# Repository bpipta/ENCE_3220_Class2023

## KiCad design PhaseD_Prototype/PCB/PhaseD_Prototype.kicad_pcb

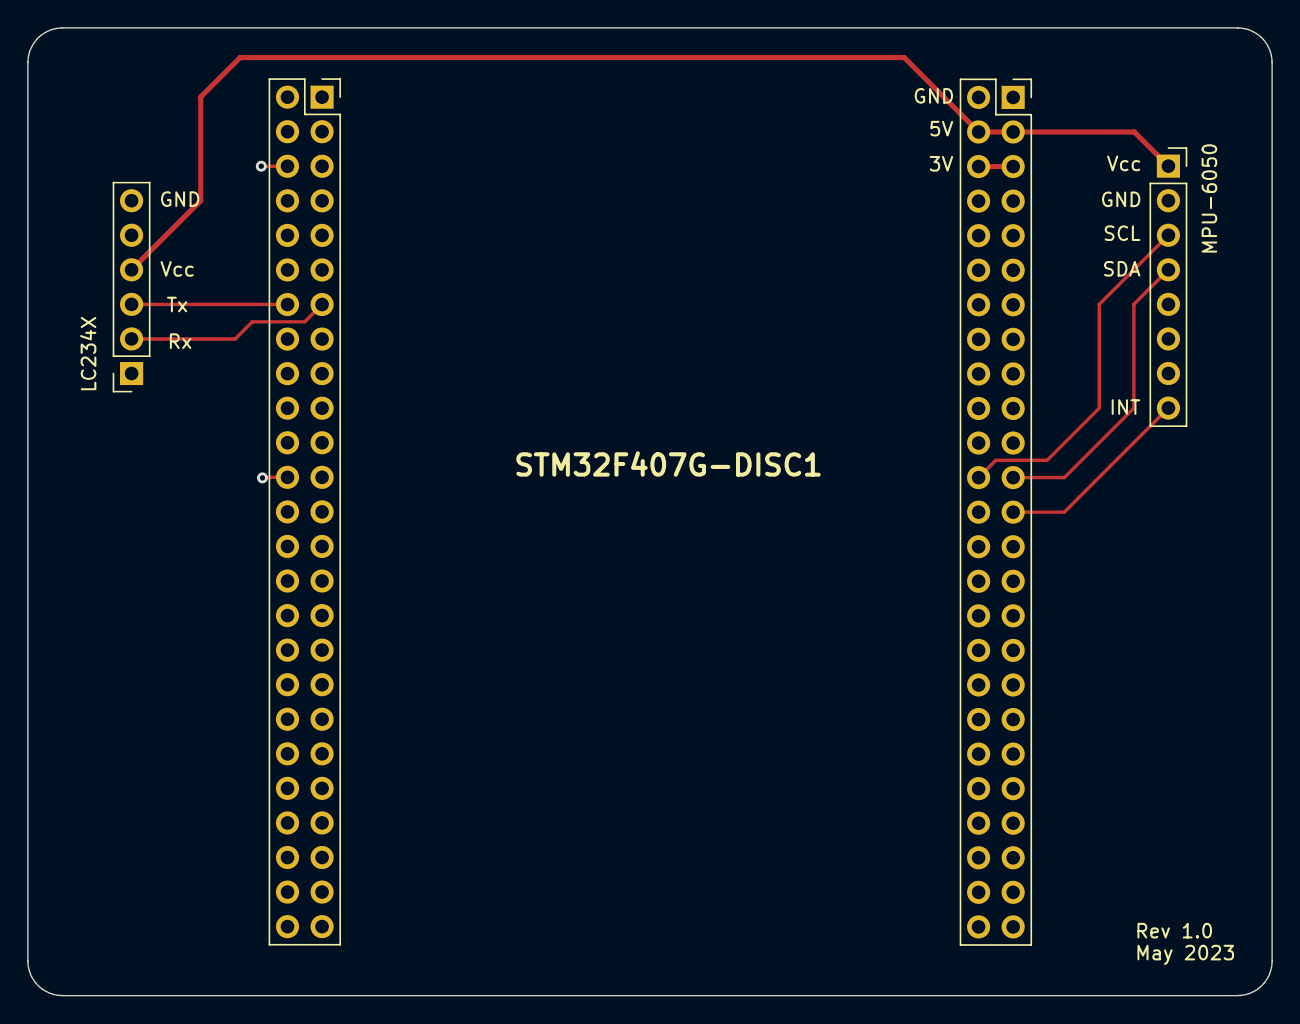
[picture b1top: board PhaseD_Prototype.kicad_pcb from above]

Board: 2 copper layers, 91.4 x 71.1 mm, 4 parts (0 on the bottom side), 8 nets.

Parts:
J1: Discovery Board Conn 1; PinSocket_2x25_P2.54mm_Vertical
J2: Discovery Board Conn 2; PinSocket_2x25_P2.54mm_Vertical
J3: MPU6050_Conn; PinSocket_1x08_P2.54mm_Vertical
J4: LC234X_Conn; PinSocket_1x06_P2.54mm_Vertical

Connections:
+3V0: J2.5, J2.6
+5V: J2.3, J2.4, J3.1, J4.4
GND: J1.1, J1.2, J1.6, J1.24, J1.49, J1.50, J2.1, J2.2, J2.49, J2.50, J3.2, J4.6
INT: J2.25, J3.8
Rx: J1.14, J4.3
SCL: J2.24, J3.3
SDA: J2.23, J3.4
Tx: J1.13, J4.2

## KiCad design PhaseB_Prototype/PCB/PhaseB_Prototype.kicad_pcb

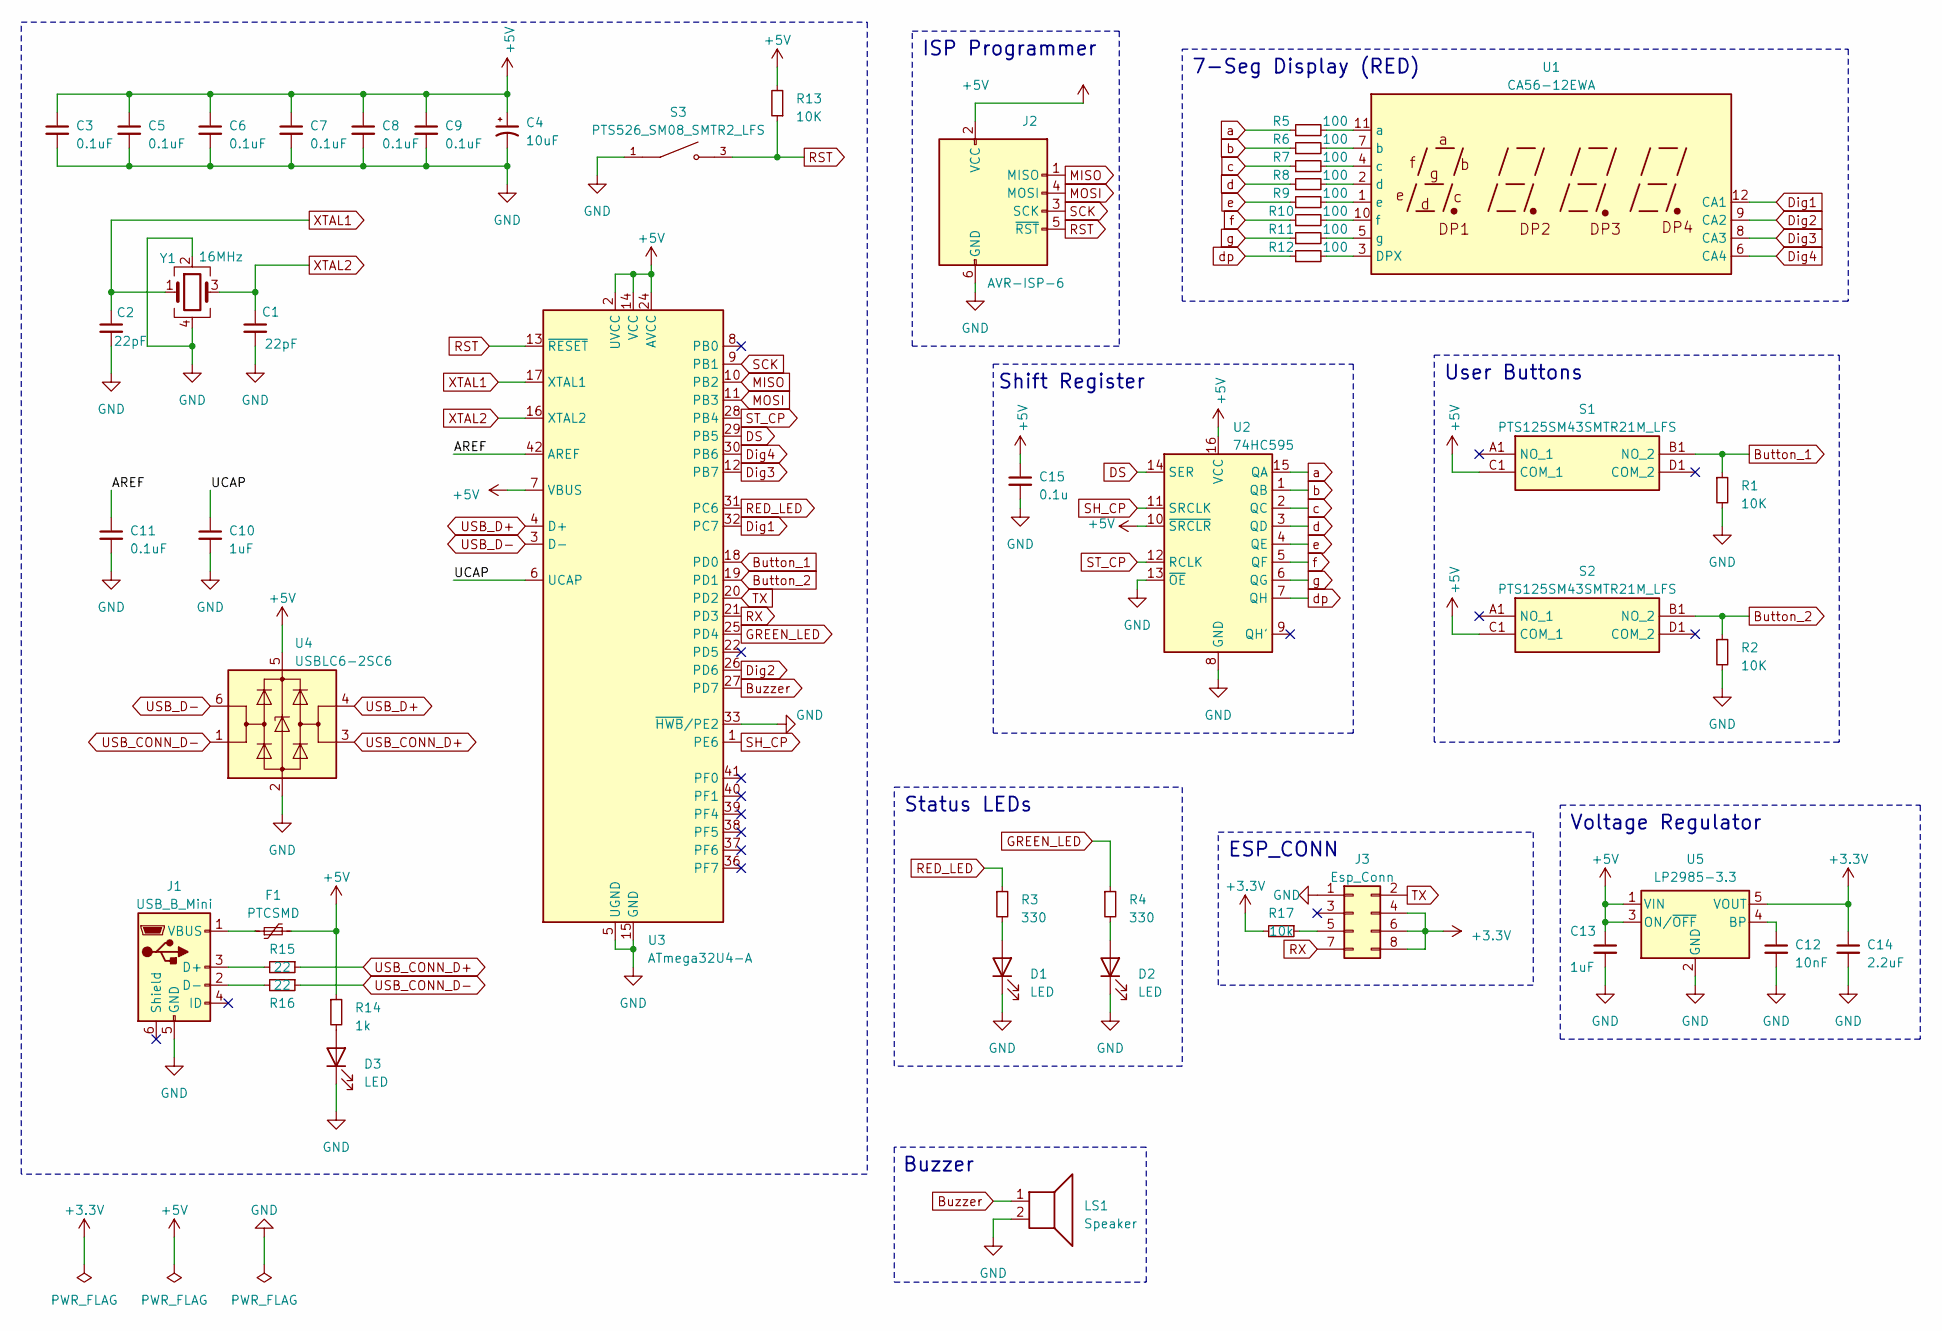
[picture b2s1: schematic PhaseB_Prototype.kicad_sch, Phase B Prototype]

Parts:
C1, C2: 22pF; C_0603_1608Metric
C3, C5, C6, C7, C8, C9, C11: 0.1uF; C_0603_1608Metric
C4: 10uF; C_0805_2012Metric
C10, C13: 1uF; C_0603_1608Metric
C12: 10nF; C_0603_1608Metric
C14: 2.2uF; C_0603_1608Metric
C15: 0.1u; C_0603_1608Metric
D1, D2, D3: LED; LED_0805_2012Metric
F1: PTCSMD; Fuse_1812_4532Metric
J1: USB_B_Mini; USB_Mini-B_Lumberg_2486_01_Horizontal
J2: AVR-ISP-6; PinSocket_2x03_P2.54mm_Vertical
J3: Esp_Conn; PinSocket_2x04_P2.54mm_Vertical
LS1: Speaker; Buzzer_12x9.5RM7.6
R1, R2, R13: 10K; R_0603_1608Metric
R3, R4: 330; R_0805_2012Metric
R5, R6, R7, R8, R9, R10, R11, R12: 100; R_0805_2012Metric
R14: 1k; R_0603_1608Metric
R15, R16: 22; R_0603_1608Metric
R17: 10k; R_0603_1608Metric
S1, S2: PTS125SM43SMTR21M_LFS; PTS125_SMD_Button; Manufacturer_Part_Number PTS125SM43SMTR21M LFS; Mouser Part Number 611-PTS125S43SMTRLFS
S3: PTS526_SM08_SMTR2_LFS; PTS526_SMD_Button; PARTREV 20 mar 19
U1: CA56-12EWA
U2: 74HC595; TSSOP-16_4.4x5mm_P0.65mm
U3: ATmega32U4-A; TQFP-44_10x10mm_P0.8mm
U4: USBLC6-2SC6; SOT-23-6
U5: LP2985-3.3; SOT-23-5
Y1: 16MHz; Crystal_SMD_Abracon_ABM8G-4Pin_3.2x2.5mm

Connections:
+3.3V: C14.1, J3.4, J3.6, J3.8, R17.2, U5.5 (VOUT)
+5V: C3.1, C4.1, C5.1, C6.1, C7.1, C8.1, C9.1, C13.1, C15.1, F1.2, J2.2 (VCC), R13.2, R14.1, S1.C1 (COM_1), S2.C1 (COM_1), U2.10 (~SRCLR), U2.16 (VCC), U3.2 (UVCC), U3.7 (VBUS), U3.14 (VCC), U3.24 (AVCC), U3.34 (VCC), U3.44 (AVCC), U4.5 (VBUS), U5.1 (VIN), U5.3 (ON/~OFF)
/AREF: C11.1, U3.42 (AREF)
/UCAP: C10.1, U3.6 (UCAP)
Button_1: R1.1, S1.B1 (NO_2), U3.18 (PD0)
Button_2: R2.1, S2.B1 (NO_2), U3.19 (PD1)
Buzzer: LS1.1, U3.27 (PD7)
DS: U2.14 (SER), U3.29 (PB5)
Dig1: U1.12 (CA1), U3.32 (PC7)
Dig2: U1.9 (CA2), U3.26 (PD6)
Dig3: U1.8 (CA3), U3.12 (PB7)
Dig4: U1.6 (CA4), U3.30 (PB6)
GND: C1.2, C2.2, C3.2, C4.2, C5.2, C6.2, C7.2, C8.2, C9.2, C10.2, C11.2, C12.2, C13.2, C14.2, C15.2, D1.1 (K), D2.1 (K), D3.1 (K), J1.5 (GND), J2.6 (GND), J3.1, LS1.2, R1.2, R2.2, S3.1, U2.8 (GND), U2.13 (~OE), U3.5 (UGND), U3.15 (GND), U3.23 (GND), U3.33 (~HWB/PE2), U3.35 (GND), U3.43 (GND), U4.2 (GND), U5.2 (GND), Y1.2, Y1.4
GREEN_LED: R4.1, U3.25 (PD4)
MISO: J2.1 (MISO), U3.10 (PB2)
MOSI: J2.4 (MOSI), U3.11 (PB3)
unnamed: D1.2 (A), R3.2
unnamed: D2.2 (A), R4.2
unnamed: D3.2 (A), R14.2
unnamed: J1.3 (D+), R15.2
unnamed: J1.2 (D-), R16.2
unnamed: F1.1, J1.1 (VBUS)
unnamed: J3.5, R17.1
unnamed: R12.2, U1.3 (DPX)
unnamed: R5.2, U1.11 (a)
unnamed: R6.2, U1.7 (b)
unnamed: R7.2, U1.4 (c)
unnamed: R8.2, U1.2 (d)
unnamed: R9.2, U1.1 (e)
unnamed: R10.2, U1.10 (f)
unnamed: R11.2, U1.5 (g)
unnamed: C12.1, U5.4 (BP)
RED_LED: R3.1, U3.31 (PC6)
RST: J2.5 (~RST), R13.1, S3.3, U3.13 (~RESET)
RX: J3.7, U3.21 (PD3)
SCK: J2.3 (SCK), U3.9 (PB1)
SH_CP: U2.11 (SRCLK), U3.1 (PE6)
ST_CP: U2.12 (RCLK), U3.28 (PB4)
TX: J3.2, U3.20 (PD2)
USB_CONN_D+: R15.1, U4.3 (I/O2)
USB_CONN_D-: R16.1, U4.1 (I/O1)
USB_D+: U3.4 (D+), U4.4 (I/O2)
USB_D-: U3.3 (D-), U4.6 (I/O1)
XTAL1: C2.1, U3.17 (XTAL1), Y1.1
XTAL2: C1.1, U3.16 (XTAL2), Y1.3
a: R5.1, U2.15 (QA)
b: R6.1, U2.1 (QB)
c: R7.1, U2.2 (QC)
d: R8.1, U2.3 (QD)
dp: R12.1, U2.7 (QH)
e: R9.1, U2.4 (QE)
f: R10.1, U2.5 (QF)
g: R11.1, U2.6 (QG)

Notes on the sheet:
Shift Register
ESP_CONN
Voltage Regulator
ISP Programmer
Status LEDs
User Buttons
Buzzer
7-Seg Display (RED)

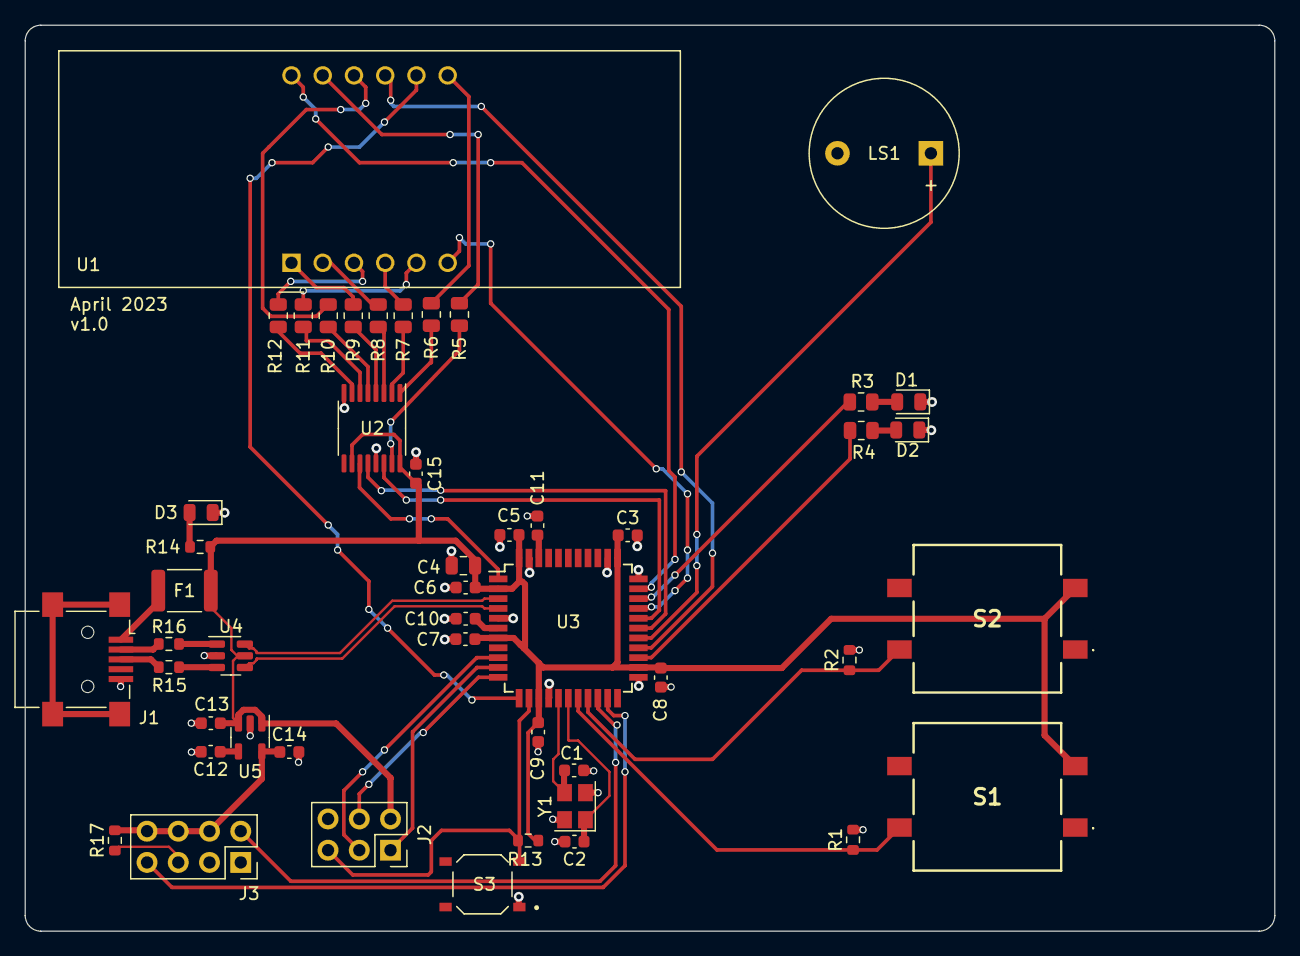
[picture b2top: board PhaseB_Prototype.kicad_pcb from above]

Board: 2 copper layers, 101.6 x 73.7 mm, 49 parts (0 on the bottom side), 53 nets.

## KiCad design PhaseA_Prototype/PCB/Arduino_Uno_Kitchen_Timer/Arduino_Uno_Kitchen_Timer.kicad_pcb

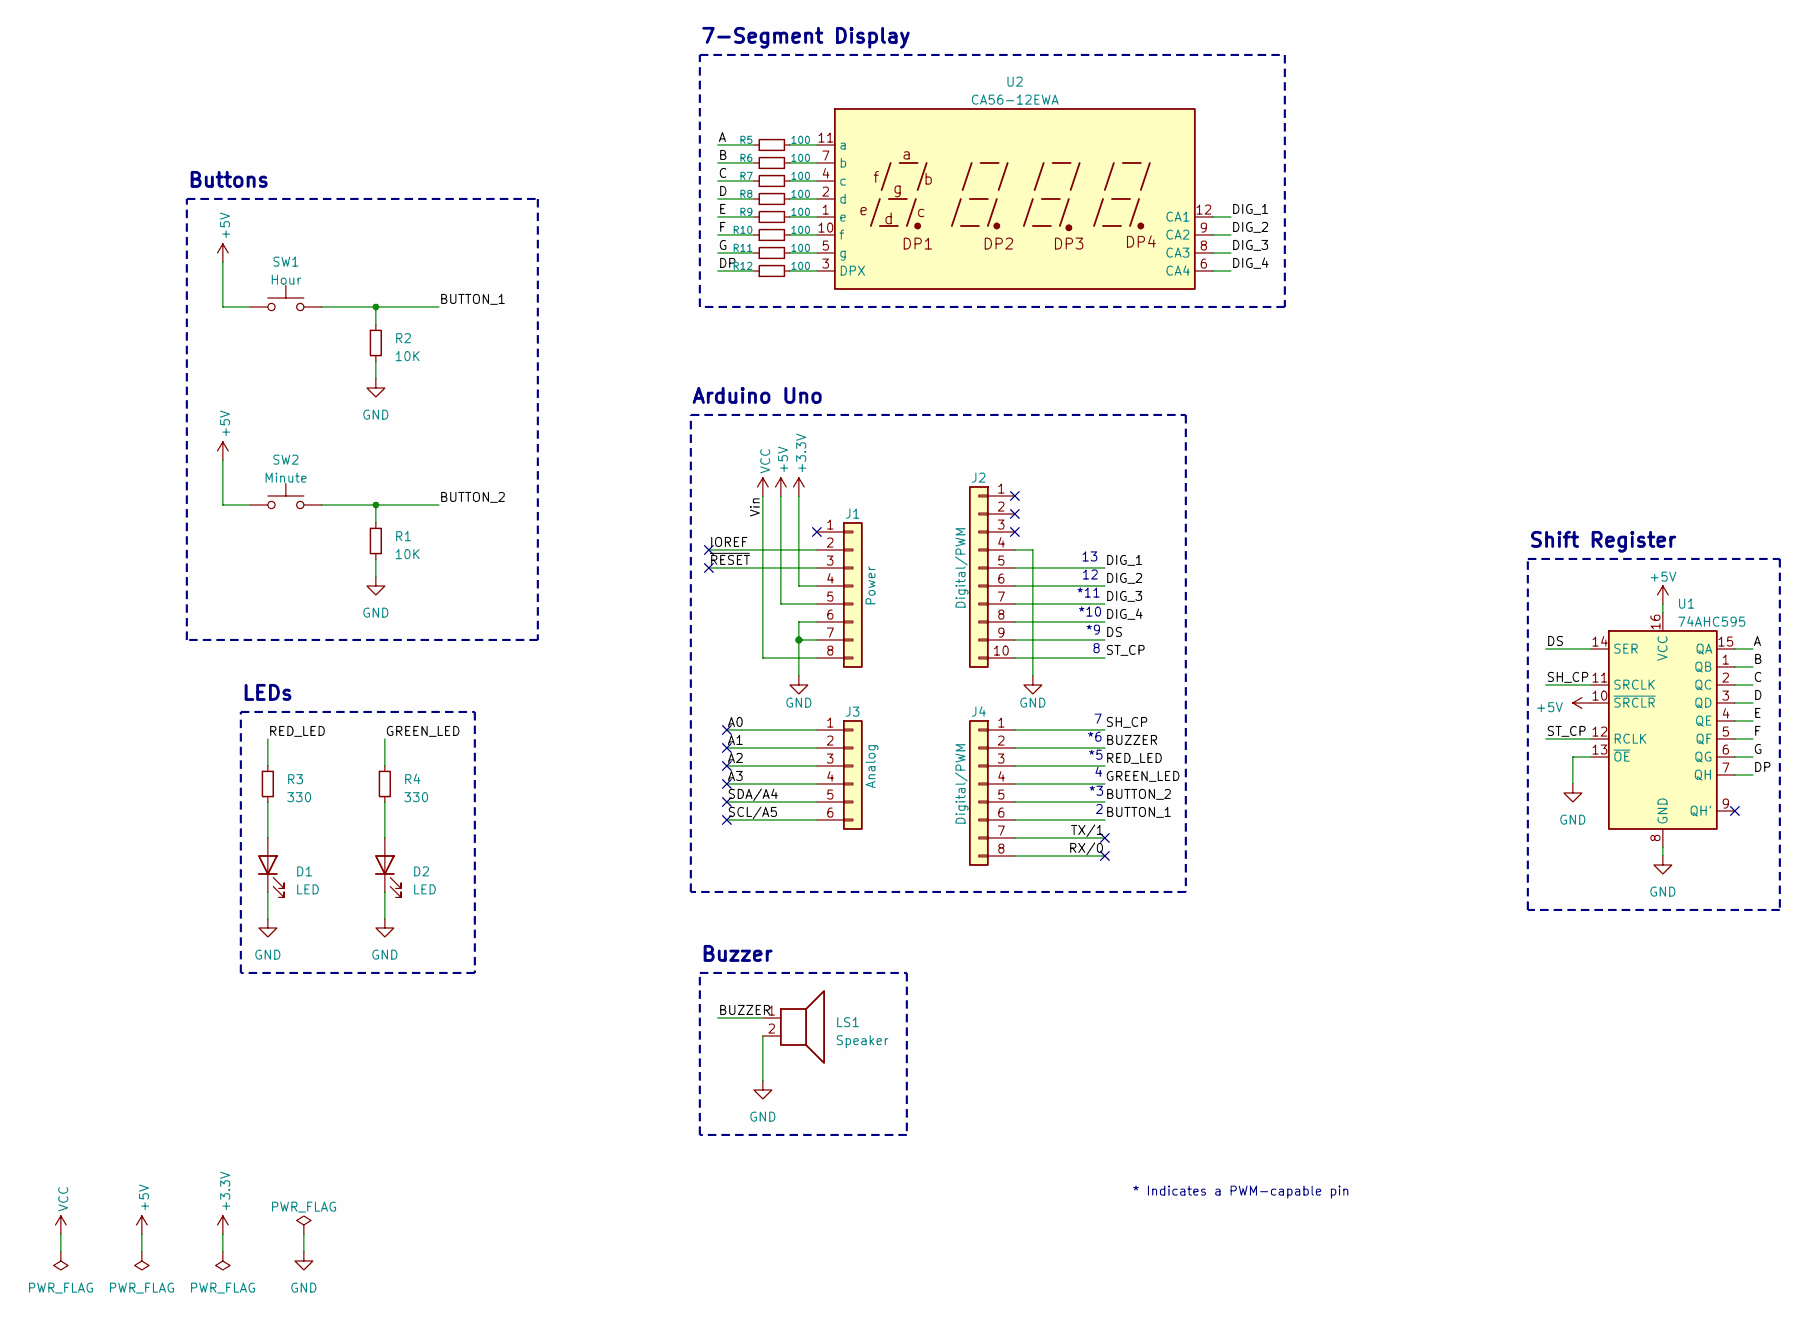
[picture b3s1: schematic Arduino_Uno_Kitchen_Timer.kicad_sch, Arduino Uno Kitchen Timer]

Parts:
D1, D2: LED; LED_D3.0mm
J1: Power; PinSocket_1x08_P2.54mm_Vertical
J2: Digital/PWM; PinSocket_1x10_P2.54mm_Vertical
J3: Analog; PinSocket_1x06_P2.54mm_Vertical
J4: Digital/PWM; PinSocket_1x08_P2.54mm_Vertical
LS1: Speaker; Buzzer_12x9.5RM7.6
R1, R2: 10K; R_Axial_DIN0207_L6.3mm_D2.5mm_P10.16mm_Horizontal
R3, R4: 330; R_Axial_DIN0207_L6.3mm_D2.5mm_P10.16mm_Horizontal
R5, R6, R7, R8, R9, R10, R11, R12: 100; R_Axial_DIN0207_L6.3mm_D2.5mm_P10.16mm_Horizontal
SW1: Hour; SW_PUSH-12mm
SW2: Minute; SW_PUSH-12mm
U1: 74AHC595; DIP-16_W7.62mm
U2: CA56-12EWA

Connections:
+3V3: J1.4
+5V: J1.5, SW1.1, SW2.1, U1.10 (~SRCLR), U1.16 (VCC)
/A: R5.1, U1.15 (QA)
/A0: J3.1
/A1: J3.2
/A2: J3.3
/A3: J3.4
/B: R6.1, U1.1 (QB)
/BUTTON_1: J4.6, R2.1, SW1.2
/BUTTON_2: J4.5, R1.1, SW2.2
/BUZZER: J4.2, LS1.1
/C: R7.1, U1.2 (QC)
/D: R8.1, U1.3 (QD)
/DIG_1: J2.5, U2.12 (CA1)
/DIG_2: J2.6, U2.9 (CA2)
/DIG_3: J2.7, U2.8 (CA3)
/DIG_4: J2.8, U2.6 (CA4)
/DP: R12.1, U1.7 (QH)
/DS: J2.9, U1.14 (SER)
/E: R9.1, U1.4 (QE)
/F: R10.1, U1.5 (QF)
/G: R11.1, U1.6 (QG)
/GREEN_LED: J4.4, R4.1
/IOREF: J1.2
/RED_LED: J4.3, R3.1
/RX/0: J4.8
/SCL/A5: J3.6
/SDA/A4: J3.5
/SH_CP: J4.1, U1.11 (SRCLK)
/ST_CP: J2.10, U1.12 (RCLK)
/TX/1: J4.7
/~RESET: J1.3
GND: D1.1 (K), D2.1 (K), J1.6, J1.7, J2.4, LS1.2, R1.2, R2.2, U1.8 (GND), U1.13 (~OE)
unnamed: D1.2 (A), R3.2
unnamed: D2.2 (A), R4.2
unnamed: R12.2, U2.3 (DPX)
unnamed: R5.2, U2.11 (a)
unnamed: R6.2, U2.7 (b)
unnamed: R7.2, U2.4 (c)
unnamed: R8.2, U2.2 (d)
unnamed: R9.2, U2.1 (e)
unnamed: R10.2, U2.10 (f)
unnamed: R11.2, U2.5 (g)
VCC: J1.8

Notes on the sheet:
Shift Register
*11
Arduino Uno
7-Segment Display
*10
* Indicates a PWM-capable pin
LEDs
Buzzer
Buttons

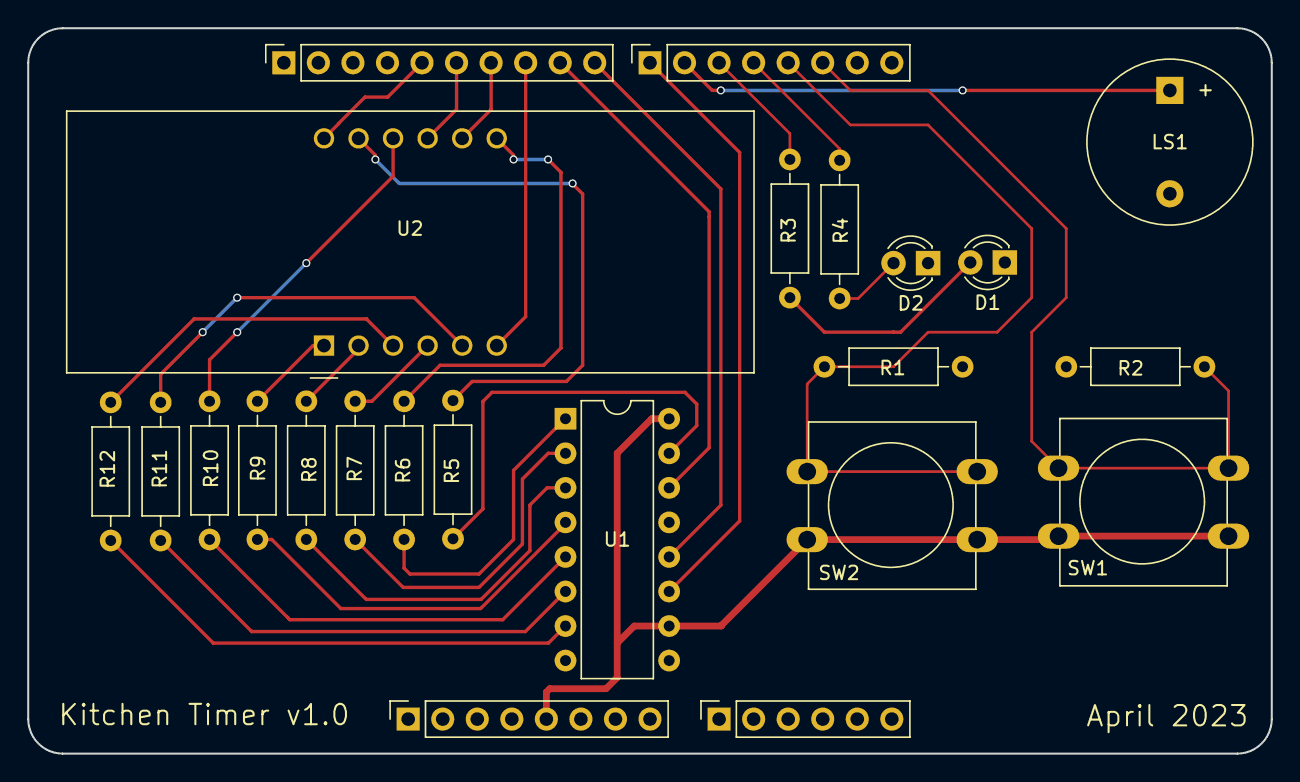
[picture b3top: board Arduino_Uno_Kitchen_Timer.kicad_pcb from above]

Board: 2 copper layers, 91.4 x 53.3 mm, 23 parts (0 on the bottom side), 32 nets.

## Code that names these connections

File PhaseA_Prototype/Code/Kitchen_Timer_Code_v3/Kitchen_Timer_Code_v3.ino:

#define BUTTON_1  2
#define BUTTON_2  3
#define GREEN_LED 4
#define RED_LED   5
#define BUZZER    6

#define DATA      9
#define LATCH     8
#define CLOCK     7

#define DIGIT_1   13
#define DIGIT_2   12
#define DIGIT_3   11
#define DIGIT_4   10

#define TIMER_1_SPEED    62500   // Timer will count one second
#define TIMER_2_SPEED    10      // Controls the rate of the display

const byte table[] = {0x3f,0x06,0x5b,0x4f,0x66,0x6d,0x7d,0x07,0x7f,0x6f};    // 7 segment encoding of numbers 0 to 9

volatile unsigned short gCount;  // Keeps track of seconds
volatile bool gTimeEnd_flag;     // Flag for when the timer ends
volatile byte gCurrentDigit;     // Controls which digit is being displayed

void setup() {
  // LEDs Pins
  pinMode(RED_LED, OUTPUT);
  pinMode(GREEN_LED, OUTPUT);

  // Button Pins
  pinMode(BUTTON_1, INPUT_PULLUP);
  attachInterrupt(digitalPinToInterrupt(BUTTON_1), Button_1_ISR, RISING);
  pinMode(BUTTON_2, INPUT_PULLUP);
  attachInterrupt(digitalPinToInterrupt(BUTTON_2), Button_2_ISR, RISING);

  // Buzzer Pins
  pinMode(BUZZER, OUTPUT);

  // 7-Seg Display
  pinMode(DIGIT_1, OUTPUT);
  pinMode(DIGIT_2, OUTPUT);
  pinMode(DIGIT_3, OUTPUT);
  pinMode(DIGIT_4, OUTPUT);

  // Shift Register Pins
  pinMode(LATCH, OUTPUT);
  pinMode(CLOCK, OUTPUT);
  pinMode(DATA, OUTPUT); 

  noInterrupts();

  // Initialize timer 1
  TCCR1A = 0;
  TCCR1B = 0;
  OCR1A = TIMER_1_SPEED;      // compare match register 16MHz/256
  TCCR1B |= (1 << WGM12);   // CTC mode
  TCCR1B |= (1 << CS12);    // 256 prescaler

  // Initialize timer 2
  TCCR2A = 0;
  TCCR2B = 0;
  OCR2A = TIMER_2_SPEED;                       // max value 2^8 - 1 = 255
  TCCR2A |= (1<<WGM21);
  TCCR2B = (1<<CS22) | (1<<CS21) | (1<<CS20); // 1204 prescaler
  TIMSK2 |= (1<<OCIE2A);

  // Set initial state of global variables and leds
  initialize_state();

  // Turn off diplay
  toggleDisplay(HIGH);
  
  interrupts();

}

/********** Functions **********/

void initialize_state()
{
  TCNT1  = 0;               // Clear count register
  TIMSK1 &= ~(1<<OCIE1A);   // Disable timer interrupts
  
  gTimeEnd_flag = 0;
  gCurrentDigit = 0;
  gCount = 0;
  
  digitalWrite(RED_LED, HIGH);
  digitalWrite(GREEN_LED, HIGH);
}

void displayNumber(unsigned char num, bool dp)
{
  digitalWrite(LATCH, LOW);
  shiftOut(DATA, CLOCK, MSBFIRST, table[num] | (dp << 7));
  digitalWrite(LATCH, HIGH);
}

void toggleDisplay(bool isOn)
{
   digitalWrite(DIGIT_1, isOn);
   digitalWrite(DIGIT_2, isOn);
   digitalWrite(DIGIT_3, isOn);
   digitalWrite(DIGIT_4, isOn);
}

void activateBuzzer()
{
    unsigned char i;
  
    for(i=0;i<100;i++) {
      digitalWrite(BUZZER,HIGH);
      delay(1);//wait for 1ms
      digitalWrite(BUZZER,LOW);
      delay(1);//wait for 1ms
    }
}

/********** Interrupt Handlers **********/

// Button1 interrupt service routine (ISR)
// Increments gCount
void Button_1_ISR()
{
  if (!gTimeEnd_flag) gCount++;               // Do not increase if timer is going off
  //This works too: gCount+=(!gTimeEnd_flag);
  if (gCount > 3599) gCount = 0;              // Check if display is over limit: 59 min 59 sec
}

// Button2 interrupt service routine (ISR)
// Toggles the Timer2 interrupt on/off and resets when gTimeEnd_flag is set
void Button_2_ISR()
{ 
  // Only toggle clock if count > 0
  if (gCount) {
      TIMSK1 ^= (1<<OCIE1A);                         // toggle timer interrupt (flip the second bit: OCIE1A)
      TCNT1  = 0;                                    // Clear the count register
      digitalWrite(RED_LED, !digitalRead(RED_LED));  // Bitmask second bit for TIMSK1 and right shift 1 instead of read?
  }
  // If time has ended and button 2 is pressed, reset
  else if (gTimeEnd_flag) {
    initialize_state();
  }
}

// Timer1 interrupt service routine (ISR)
// Decreaments gCount
ISR(TIMER1_COMPA_vect)
{
  gCount--; 
  
  // Check when the timer reaches 0
  if (!gCount) {
    TIMSK1 &= ~(1<<OCIE1A);     // Disable timer interrupt
    gTimeEnd_flag = 1;
  }
}

// Timer2 interrupt service routine (ISR)
// Writes the correct digit to the correct 7 seg display
ISR(TIMER2_COMPA_vect)   
{
  toggleDisplay(HIGH);
  switch (gCurrentDigit)
  {
    case 1: //0x:xx
      displayNumber( int(gCount / 600), 0 );   // prepare to display digit 1 (most left)
      digitalWrite(DIGIT_1, LOW);  // turn on digit 1
      break;
 
    case 2: //x0:xx
      displayNumber( int(gCount / 60) % 10, 1 );   // prepare to display digit 2
      digitalWrite(DIGIT_2, LOW);     // turn on digit 2
      break;
 
    case 3: //xx:0x
      displayNumber( (gCount / 10) % 6, 0 );   // prepare to display digit 3
      digitalWrite(DIGIT_3, LOW);    // turn on digit 3
      break;
 
    case 4: //xx:x0
      displayNumber((gCount % 10), 0); // prepare to display digit 4 (most right)
      digitalWrite(DIGIT_4, LOW);  // turn on digit 4
  }
  gCurrentDigit = (gCurrentDigit % 4) + 1;
}

/********** Main Loop **********/

void loop() {

  if (gTimeEnd_flag) {

    toggleDisplay(LOW);

    digitalWrite(GREEN_LED, LOW);
    digitalWrite(RED_LED, HIGH);

    while(gTimeEnd_flag) {
      activateBuzzer();
    }
  }
}

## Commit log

2023-04-12 Completed Phase A: Kitchen Timer v1.0
2023-04-12 Initial commit for Phase B
2023-04-13 Completed schematic for Phase B
2023-04-21 Completed PCB for Phase B
2023-04-21 Renamed pcb screenshots
2023-04-27 Added 3d models to buttons on PhaseB PCB
2023-05-04 Completed Phase B Beta
2023-05-31 Work on Phase D Prototype
2023-06-09 Added Phase B Report
2023-06-09 Changed images in Phase B Report
